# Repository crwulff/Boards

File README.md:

# Boards
1. [Pano G2 Debug Adapter](/PanoDebugAdapter) converts the 0.05" JTAG connector on these devices to 0.1" to connect to fly leads or other jumper wires.

<br/>

2. [Layer 1 Switch](/L1Switch) is a L1 switch / virtual patch panel development board. This is useful for automated testing of equipment that needs different network topologies for various tests.

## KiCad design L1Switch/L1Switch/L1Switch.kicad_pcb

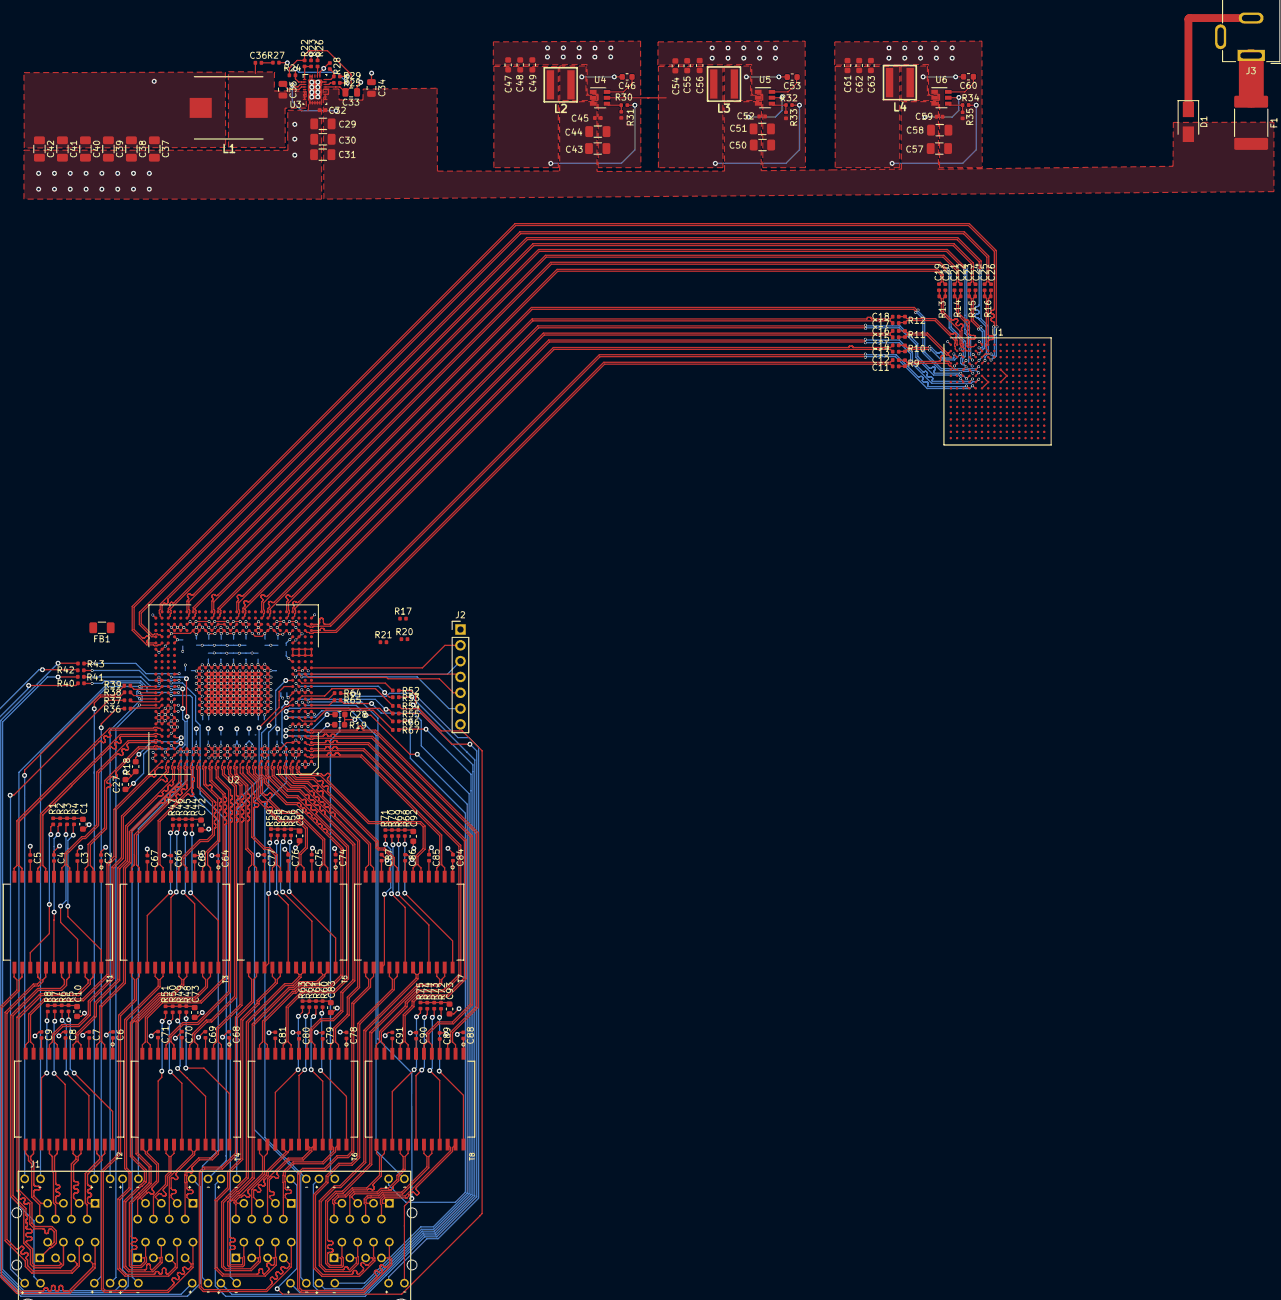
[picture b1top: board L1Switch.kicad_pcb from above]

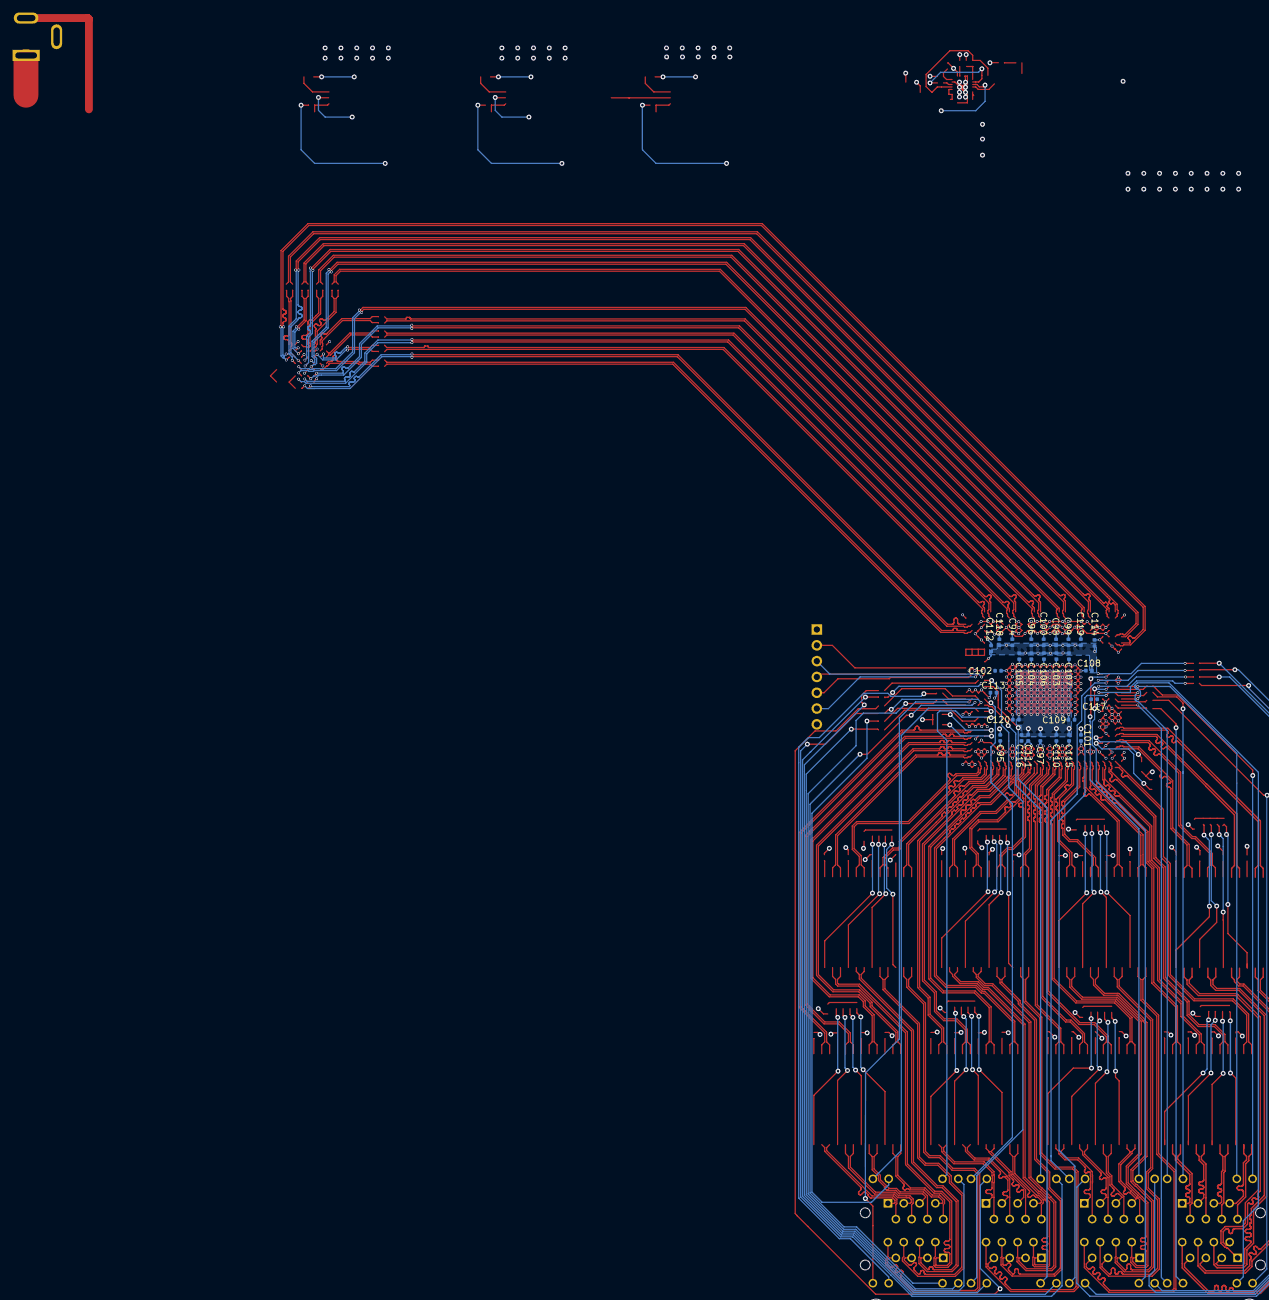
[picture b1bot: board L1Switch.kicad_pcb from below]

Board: 4 copper layers, 219 parts (27 on the bottom side), 338 nets.

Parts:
C1, C10, C72, C73, C82, C83, C92, C93: 1000pF, 2KV; C_0603_1608Metric
C2, C3, C4, C5, C6, C7, C8, C9, C11, C12, C13, C14, C15, C16, C17, C18, C19, C20, C21, C22, C23, C24, C25, C26, C64, C65, C66, C67, C68, C69, C70, C71, C74, C75, C76, C77, C78, C79, C80, C81, C84, C85, C86, C87, C88, C89, C90, C91: 0.1 uF; C_0402_1005Metric
C27, C28: 1.0 uF; C_0603_1608Metric
C29, C30, C31: 22 uF, 3.637 mΩ; C_1206_3216Metric
C32: 2.2 nF, 1.268 Ω; C_0402_1005Metric
C33, C34: 2.2 uF, 9.497 mΩ; C_0805_2012Metric
C35: 100 nF, 64 mOhm; C_0805_2012Metric
C36: 470 pF, 5.548 Ω; C_0402_1005Metric
C37, C38, C39, C40, C41, C42: 100 uF, 4.885 mΩ; C_1206_3216Metric
C43, C44, C50, C51, C57, C58: 10 uF, 4.512 mΩ; C_1206_3216Metric
C45, C52, C59: 100 nF, 1 mΩ; C_0402_1005Metric
C46, C53, C60: 100 nF, 1 mOhm; C_0603_1608Metric
C47, C48, C49, C54, C55, C56, C61, C62, C63: 22 uF, 1 mΩ; C_0603_1608Metric
C94, C95, C96, C97, C98, C99, C100, C101, C102, C103, C104, C105, C106, C107, C108, C109, C110, C111, C112, C113, C114, C115, C116, C117, C118, C119, C120: 100nF; C_0402_1005Metric
D1: P4SMA6.8CA; D_SMA
F1: 2920L700/12MR-A; Fuse_2920_7451Metric
FB1: 100 ohm @ 100 MHz, 3A; FB_1206_3216Metric
J1: RJSNEGF8A08; AMPHENOL_RJSNE-GF8X-08
J2: Conn_01x07_Male; PinHeader_1x07_P2.54mm_Vertical
J3: Barrel_Jack; MJ-179PH
L1: 1 uH, 3.5 mΩ; INDPM110100X400N
L2, L3, L4: 2.2 uH, 13.2 mΩ; XAL5030
R1, R2, R3, R4, R5, R6, R7, R8, R36, R37, R38, R39, R40, R41, R42, R43, R44, R45, R46, R47, R48, R49, R50, R51, R52, R53, R54, R55, R56, R57, R58, R59, R60, R61, R62, R63, R64, R65, R66, R67, R68, R69, R70, R71, R72, R73, R74, R75: 75R0; R_0402_1005Metric
R9, R10, R11, R12, R13, R14, R15, R16: 100R0; R_0402_1005Metric
R17, R20, R28, R29, R31, R33, R35: 10K; R_0402_1005Metric
R18, R19: 2K00 1%; R_0603_1608Metric
R21: 1K0; R_0402_1005Metric
R22: 249K; R_0402_1005Metric
R23: 44K2; R_0402_1005Metric
R24: 105K; R_0402_1005Metric
R25: 150K; R_0402_1005Metric
R26: 68K1; R_0402_1005Metric
R27: 3R01; R_0402_1005Metric
R30: 33K2; R_0402_1005Metric
R32: 13K7; R_0402_1005Metric
R34: 3K09; R_0402_1005Metric
T1, T2, T3, T4, T5, T6, T7, T8: SM51589PEL
U1: XC7A15T-FTG256; Xilinx_FTG256
U2: VSC8658
U3: TPS548A20RVE; TPS548A20RVER
U4, U5, U6: TPS565208; SOT-23-6

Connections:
+1V0: C61.1, C62.1, C63.1, L4.2, R34.1, U1.E10 (VCCBRAM), U1.F7 (VCCINT), U1.F9 (VCCINT), U1.F11 (VCCBRAM), U1.G6 (VCCINT), U1.H9 (VCCINT), U1.J6 (VCCINT), U1.K9 (VCCINT), U1.L8 (VCCINT)
+1V2: C37.1, C38.1, C39.1, C40.1, C41.1, C42.1, C102.1, C103.1, C104.1, C105.1, C106.1, C107.1, C108.1, C109.1, C120.1, FB1.2, L1.2, R28.1, U1.A6 (VCCO_35), U1.A16 (VCCO_15), U1.B3 (VCCO_35), U1.B13 (VCCO_15), U1.C10 (VCCO_15), U1.D7 (VCCO_35), U1.E4 (VCCO_35), U1.E14 (VCCO_15), U1.F1 (VCCO_35), U1.H15 (VCCO_15), U1.J2 (VCCO_35), U1.J12 (VCCO_15), U1.L16 (VCCO_14), U1.M13 (VCCO_14), U1.N10 (VCCO_14), U1.P7 (VCCO_14), U1.R14 (VCCO_14), U1.T11 (VCCO_14), U2.K8 (VDD12), U2.K19 (VDD12), U2.L8 (VDD12), U2.L19 (VDD12), U2.M8 (VDD12), U2.M19 (VDD12), U2.N8 (VDD12), U2.N19 (VDD12), U2.P8 (VDD12), U2.P19 (VDD12), U2.R8 (VDD12), U2.R19 (VDD12), U2.T8 (VDD12), U2.T19 (VDD12), U2.U8 (VDD12), U2.U9 (VDD12), U2.U10 (VDD12), U2.U11 (VDD12), U2.U12 (VDD12), U2.U13 (VDD12), U2.U14 (VDD12), U2.U15 (VDD12), U2.U16 (VDD12), U2.U17 (VDD12), U2.U18 (VDD12), U2.U19 (VDD12), U3.24 (VO)
+1V2A: C94.1, C95.1, C96.1, C97.1, C98.1, C99.1, C100.1, C101.1, C118.1, C119.1, FB1.1, U2.AB24 (VDD12A), U2.AC4 (VDD12A), U2.AC5 (VDD12A), U2.AC7 (VDD12A), U2.AC8 (VDD12A), U2.AC11 (VDD12A), U2.AC12 (VDD12A), U2.AC13 (VDD12A), U2.AC15 (VDD12A), U2.AC16 (VDD12A), U2.AC18 (VDD12A), U2.AC19 (VDD12A), U2.AC20 (VDD12A), U2.AC24 (VDD12A), U2.AD8 (VDD12A), U2.AD19 (VDD12A), U2.C7 (VDD12A), U2.C13 (VDD12A), U2.C19 (VDD12A), U2.C20 (VDD12A), U2.D6 (VDD12A), U2.D7 (VDD12A), U2.D13 (VDD12A), U2.D19 (VDD12A), U2.D20 (VDD12A), U2.D23 (VDD12A), U2.E3 (VDD12A), U2.E4 (VDD12A), U2.E24 (VDD12A)
+1V8: C54.1, C55.1, C56.1, L3.2, R32.1, U1.F8 (VCCBATT_0), U1.G8 (VCCADC_0), U1.G10 (VCCAUX), U1.J10 (VCCAUX), U1.K11 (VCCAUX), U1.L10 (VCCAUX), U4.5 (EN)
+3V3: C47.1, C48.1, C49.1, C110.1, C111.1, C112.1, C113.1, C114.1, C115.1, C116.1, C117.1, J2.1, L2.2, R17.2, R20.1, R21.1, R30.1, U1.M3 (VCCO_34), U1.R4 (VCCO_34), U1.T1 (VCCO_34), U2.AA23 (VDD33), U2.AB4 (VDDIO), U2.AB23 (VDD33), U2.AD3 (VDD33), U2.AD5 (VDD33), U2.AD7 (VDD33), U2.AD11 (VDD33), U2.AD12 (VDD33), U2.AD14 (VDD33), U2.AD17 (VDD33), U2.AD20 (VDD33), U2.AD21 (VDD33), U2.C3 (VDD33), U2.C4 (VDD33), U2.C10 (VDD33), U2.C11 (VDD33), U2.C12 (VDD33), U2.C16 (VDD33), U2.C17 (VDD33), U2.C21 (VDD33), U2.C23 (VDD33), U2.C25 (VDD33), U2.D3 (VDD33), U2.D4 (VDD33), U2.D10 (VDD33), U2.D11 (VDD33), U2.D12 (VDD33), U2.D16 (VDD33), U2.D17 (VDD33), U2.D21 (VDD33), U2.D22 (VDD33), U2.F24 (VDD33), U2.G23 (VDD33), U2.H23 (VDD33), U2.H24 (VDD33), U2.J23 (VDD33), U2.M23 (VDD33), U2.M24 (VDD33), U2.N1 (VDD33), U2.N2 (VDD33), U2.N3 (VDD33), U2.N4 (VDD33), U2.R25 (VDD33), U2.R26 (VDD33), U2.U2 (VDDIO), U2.U4 (VDD33), U2.V2 (VDDIO)
/Net 1/P1.A+: J1.11 (1-1), T1.23 (TD1+)
/Net 1/P1.A-: J1.12 (1-2), T1.22 (TD1-)
/Net 1/P1.A_CMN: R4.1, T1.24 (TCT1)
/Net 1/P1.B+: J1.13 (1-3), T1.20 (TD2+)
/Net 1/P1.B-: J1.14 (1-4), T1.19 (TD2-)
/Net 1/P1.B_CMN: R3.1, T1.21 (TCT2)
/Net 1/P1.C+: J1.15 (1-5), T1.17 (TD3+)
/Net 1/P1.C-: J1.16 (1-6), T1.16 (TD3-)
/Net 1/P1.C_CMN: R2.1, T1.18 (TCT3)
/Net 1/P1.D+: J1.17 (1-7), T1.14 (TD4+)
/Net 1/P1.D-: J1.18 (1-8), T1.13 (TD4-)
/Net 1/P1.D_CMN: R1.1, T1.15 (TCT4)
/Net 1/P1.LED0: J1.19 (1-9), U2.L26 (LED_0_0)
/Net 1/P1.LED1: R36.1, U2.L25 (LED_0_1)
/Net 1/P1.LED2: J1.111 (1-11), U2.M26 (LED_0_2)
/Net 1/P1.LED3: R37.1, U2.M25 (LED_0_3)
/Net 1/P2.A+: J1.21 (2-1), T2.23 (TD1+)
/Net 1/P2.A-: J1.22 (2-2), T2.22 (TD1-)
/Net 1/P2.A_CMN: R5.1, T2.24 (TCT1)
/Net 1/P2.B+: J1.23 (2-3), T2.20 (TD2+)
/Net 1/P2.B-: J1.24 (2-4), T2.19 (TD2-)
/Net 1/P2.B_CMN: R6.1, T2.21 (TCT2)
/Net 1/P2.C+: J1.25 (2-5), T2.17 (TD3+)
/Net 1/P2.C-: J1.26 (2-6), T2.16 (TD3-)
/Net 1/P2.C_CMN: R7.1, T2.18 (TCT3)
/Net 1/P2.D+: J1.27 (2-7), T2.14 (TD4+)
/Net 1/P2.D-: J1.28 (2-8), T2.13 (TD4-)
/Net 1/P2.D_CMN: R8.1, T2.15 (TCT4)
/Net 1/P2.LED0: J1.29 (2-9), U2.N26 (LED_1_0)
/Net 1/P2.LED1: R38.1, U2.N25 (LED_1_1)
/Net 1/P2.LED2: J1.211 (2-11), U2.P26 (LED_1_2)
/Net 1/P2.LED3: R39.1, U2.P25 (LED_1_3)
/Net 1/P3.A+: J1.31 (3-1), T3.23 (TD1+)
/Net 1/P3.A-: J1.32 (3-2), T3.22 (TD1-)
/Net 1/P3.A_CMN: R44.1, T3.24 (TCT1)
/Net 1/P3.B+: J1.33 (3-3), T3.20 (TD2+)
/Net 1/P3.B-: J1.34 (3-4), T3.19 (TD2-)
/Net 1/P3.B_CMN: R45.1, T3.21 (TCT2)
/Net 1/P3.C+: J1.35 (3-5), T3.17 (TD3+)
/Net 1/P3.C-: J1.36 (3-6), T3.16 (TD3-)
/Net 1/P3.C_CMN: R46.1, T3.18 (TCT3)
/Net 1/P3.D+: J1.37 (3-7), T3.14 (TD4+)
/Net 1/P3.D-: J1.38 (3-8), T3.13 (TD4-)
/Net 1/P3.D_CMN: R47.1, T3.15 (TCT4)
/Net 1/P3.LED0: J1.39 (3-9), U2.N24 (LED_2_0)
/Net 1/P3.LED1: R40.1, U2.N23 (LED_2_1)
/Net 1/P3.LED2: J1.311 (3-11), U2.P24 (LED_2_2)
/Net 1/P3.LED3: R41.1, U2.P23 (LED_2_3)
/Net 1/P4.A+: J1.41 (4-1), T4.23 (TD1+)
/Net 1/P4.A-: J1.42 (4-2), T4.22 (TD1-)
/Net 1/P4.A_CMN: R48.1, T4.24 (TCT1)
/Net 1/P4.B+: J1.43 (4-3), T4.20 (TD2+)
/Net 1/P4.B-: J1.44 (4-4), T4.19 (TD2-)
/Net 1/P4.B_CMN: R49.1, T4.21 (TCT2)
/Net 1/P4.C+: J1.45 (4-5), T4.17 (TD3+)
/Net 1/P4.C-: J1.46 (4-6), T4.16 (TD3-)
/Net 1/P4.C_CMN: R50.1, T4.18 (TCT3)
/Net 1/P4.D+: J1.47 (4-7), T4.14 (TD4+)
/Net 1/P4.D-: J1.48 (4-8), T4.13 (TD4-)
/Net 1/P4.D_CMN: R51.1, T4.15 (TCT4)
/Net 1/P4.LED0: J1.49 (4-9), U2.R24 (LED_3_0)
/Net 1/P4.LED1: R42.1, U2.R23 (LED_3_1)
/Net 1/P4.LED2: J1.411 (4-11), U2.T24 (LED_3_2)
/Net 1/P4.LED3: R43.1, U2.T23 (LED_3_3)
/Net 1/P5.A+: J1.51 (5-1), T5.23 (TD1+)
/Net 1/P5.A-: J1.52 (5-2), T5.22 (TD1-)
/Net 1/P5.A_CMN: R56.1, T5.24 (TCT1)
/Net 1/P5.B+: J1.53 (5-3), T5.20 (TD2+)
/Net 1/P5.B-: J1.54 (5-4), T5.19 (TD2-)
/Net 1/P5.B_CMN: R57.1, T5.21 (TCT2)
/Net 1/P5.C+: J1.55 (5-5), T5.17 (TD3+)
/Net 1/P5.C-: J1.56 (5-6), T5.16 (TD3-)
/Net 1/P5.C_CMN: R58.1, T5.18 (TCT3)
/Net 1/P5.D+: J1.57 (5-7), T5.14 (TD4+)
/Net 1/P5.D-: J1.58 (5-8), T5.13 (TD4-)
/Net 1/P5.D_CMN: R59.1, T5.15 (TCT4)
/Net 1/P5.LED0: J1.59 (5-9), U2.R4 (LED_4_0)
/Net 1/P5.LED1: R52.1, U2.R3 (LED_4_1)
/Net 1/P5.LED2: J1.511 (5-11), U2.P4 (LED_4_2)
/Net 1/P5.LED3: R53.1, U2.P3 (LED_4_3)
/Net 1/P6.A+: J1.61 (6-1), T6.23 (TD1+)
/Net 1/P6.A-: J1.62 (6-2), T6.22 (TD1-)
/Net 1/P6.A_CMN: R60.1, T6.24 (TCT1)
/Net 1/P6.B+: J1.63 (6-3), T6.20 (TD2+)
/Net 1/P6.B-: J1.64 (6-4), T6.19 (TD2-)
/Net 1/P6.B_CMN: R61.1, T6.21 (TCT2)
/Net 1/P6.C+: J1.65 (6-5), T6.17 (TD3+)
/Net 1/P6.C-: J1.66 (6-6), T6.16 (TD3-)
/Net 1/P6.C_CMN: R62.1, T6.18 (TCT3)
/Net 1/P6.D+: J1.67 (6-7), T6.14 (TD4+)
/Net 1/P6.D-: J1.68 (6-8), T6.13 (TD4-)
/Net 1/P6.D_CMN: R63.1, T6.15 (TCT4)
/Net 1/P6.LED0: J1.69 (6-9), U2.M4 (LED_5_0)
/Net 1/P6.LED1: R54.1, U2.M3 (LED_5_1)
/Net 1/P6.LED2: J1.611 (6-11), U2.L4 (LED_5_2)
/Net 1/P6.LED3: R55.1, U2.L3 (LED_5_3)
/Net 1/P7.A+: J1.71 (7-1), T7.23 (TD1+)
/Net 1/P7.A-: J1.72 (7-2), T7.22 (TD1-)
/Net 1/P7.A_CMN: R68.1, T7.24 (TCT1)
/Net 1/P7.B+: J1.73 (7-3), T7.20 (TD2+)
/Net 1/P7.B-: J1.74 (7-4), T7.19 (TD2-)
/Net 1/P7.B_CMN: R69.1, T7.21 (TCT2)
/Net 1/P7.C+: J1.75 (7-5), T7.17 (TD3+)
/Net 1/P7.C-: J1.76 (7-6), T7.16 (TD3-)
/Net 1/P7.C_CMN: R70.1, T7.18 (TCT3)
/Net 1/P7.D+: J1.77 (7-7), T7.14 (TD4+)
/Net 1/P7.D-: J1.78 (7-8), T7.13 (TD4-)
/Net 1/P7.D_CMN: R71.1, T7.15 (TCT4)
/Net 1/P7.LED0: J1.79 (7-9), U2.M2 (LED_6_0)
/Net 1/P7.LED1: R64.1, U2.M1 (LED_6_1)
/Net 1/P7.LED2: J1.711 (7-11), U2.L2 (LED_6_2)
/Net 1/P7.LED3: R65.1, U2.L1 (LED_6_3)
/Net 1/P8.A+: J1.81 (8-1), T8.23 (TD1+)
/Net 1/P8.A-: J1.82 (8-2), T8.22 (TD1-)
/Net 1/P8.A_CMN: R72.1, T8.24 (TCT1)
/Net 1/P8.B+: J1.83 (8-3), T8.20 (TD2+)
/Net 1/P8.B-: J1.84 (8-4), T8.19 (TD2-)
/Net 1/P8.B_CMN: R73.1, T8.21 (TCT2)
/Net 1/P8.C+: J1.85 (8-5), T8.17 (TD3+)
/Net 1/P8.C-: J1.86 (8-6), T8.16 (TD3-)
/Net 1/P8.C_CMN: R74.1, T8.18 (TCT3)
/Net 1/P8.D+: J1.87 (8-7), T8.14 (TD4+)
/Net 1/P8.D-: J1.88 (8-8), T8.13 (TD4-)
/Net 1/P8.D_CMN: R75.1, T8.15 (TCT4)
/Net 1/P8.LED0: J1.89 (8-9), U2.K4 (LED_7_0)
/Net 1/P8.LED1: R66.1, U2.K3 (LED_7_1)
/Net 1/P8.LED2: J1.811 (8-11), U2.J4 (LED_7_2)
/Net 1/P8.LED3: R67.1, U2.J3 (LED_7_3)
/Net 1/RD_N0: C26.2, U2.AB26 (MAC_RDN_0)
/Net 1/RD_N1: C24.2, U2.AF24 (MAC_RDN_1)
/Net 1/RD_N2: C22.2, U2.AF20 (MAC_RDN_2)
/Net 1/RD_N3: C20.2, U2.AF16 (MAC_RDN_3)
/Net 1/RD_N4: C18.2, U2.AF12 (MAC_RDN_4)
/Net 1/RD_N5: C16.2, U2.AF8 (MAC_RDN_5)
/Net 1/RD_N6: C14.2, U2.AF4 (MAC_RDN_6)
/Net 1/RD_N7: C12.2, U2.AC1 (MAC_RDN_7)
/Net 1/RD_P0: C25.2, U2.AB25 (MAC_RDP_0)
/Net 1/RD_P1: C23.2, U2.AE24 (MAC_RDP_1)
/Net 1/RD_P2: C21.2, U2.AE20 (MAC_RDP_2)
/Net 1/RD_P3: C19.2, U2.AE16 (MAC_RDP_3)
/Net 1/RD_P4: C17.2, U2.AE12 (MAC_RDP_4)
/Net 1/RD_P5: C15.2, U2.AE8 (MAC_RDP_5)
/Net 1/RD_P6: C13.2, U2.AE4 (MAC_RDP_6)
/Net 1/RD_P7: C11.2, U2.AC2 (MAC_RDP_7)
/Net 1/TXVA_N0: T1.3 (MX1-), U2.D25 (TXVNA_0)
/Net 1/TXVA_N1: T2.3 (MX1-), U2.B22 (TXVNA_1)
/Net 1/TXVA_N2: T3.3 (MX1-), U2.B18 (TXVNA_2)
/Net 1/TXVA_N3: T4.3 (MX1-), U2.B14 (TXVNA_3)
/Net 1/TXVA_N4: T5.3 (MX1-), U2.B10 (TXVNA_4)
/Net 1/TXVA_N5: T6.3 (MX1-), U2.B6 (TXVNA_5)
/Net 1/TXVA_N6: T7.3 (MX1-), U2.C2 (TXVNA_6)
/Net 1/TXVA_N7: T8.3 (MX1-), U2.G2 (TXVNA_7)
/Net 1/TXVA_P0: T1.2 (MX1+), U2.D26 (TXVPA_0)
/Net 1/TXVA_P1: T2.2 (MX1+), U2.A22 (TXVPA_1)
/Net 1/TXVA_P2: T3.2 (MX1+), U2.A18 (TXVPA_2)
/Net 1/TXVA_P3: T4.2 (MX1+), U2.A14 (TXVPA_3)
/Net 1/TXVA_P4: T5.2 (MX1+), U2.A10 (TXVPA_4)
/Net 1/TXVA_P5: T6.2 (MX1+), U2.A6 (TXVPA_5)
/Net 1/TXVA_P6: T7.2 (MX1+), U2.C1 (TXVPA_6)
/Net 1/TXVA_P7: T8.2 (MX1+), U2.G1 (TXVPA_7)
/Net 1/TXVB_N0: T1.6 (MX2-), U2.E25 (TXVNB_0)
/Net 1/TXVB_N1: T2.6 (MX2-), U2.B23 (TXVNB_1)
/Net 1/TXVB_N2: T3.6 (MX2-), U2.B19 (TXVNB_2)
/Net 1/TXVB_N3: T4.6 (MX2-), U2.B15 (TXVNB_3)
/Net 1/TXVB_N4: T5.6 (MX2-), U2.B11 (TXVNB_4)
/Net 1/TXVB_N5: T6.6 (MX2-), U2.B7 (TXVNB_5)
/Net 1/TXVB_N6: T7.6 (MX2-), U2.B3 (TXVNB_6)
/Net 1/TXVB_N7: T8.6 (MX2-), U2.F2 (TXVNB_7)
/Net 1/TXVB_P0: T1.5 (MX2+), U2.E26 (TXVPB_0)
/Net 1/TXVB_P1: T2.5 (MX2+), U2.A23 (TXVPB_1)
/Net 1/TXVB_P2: T3.5 (MX2+), U2.A19 (TXVPB_2)
/Net 1/TXVB_P3: T4.5 (MX2+), U2.A15 (TXVPB_3)
/Net 1/TXVB_P4: T5.5 (MX2+), U2.A11 (TXVPB_4)
/Net 1/TXVB_P5: T6.5 (MX2+), U2.A7 (TXVPB_5)
/Net 1/TXVB_P6: T7.5 (MX2+), U2.A3 (TXVPB_6)
/Net 1/TXVB_P7: T8.5 (MX2+), U2.F1 (TXVPB_7)
/Net 1/TXVC_N0: T1.9 (MX3-), U2.F25 (TXVNC_0)
/Net 1/TXVC_N1: T2.9 (MX3-), U2.B24 (TXVNC_1)
/Net 1/TXVC_N2: T3.9 (MX3-), U2.B20 (TXVNC_2)
/Net 1/TXVC_N3: T4.9 (MX3-), U2.B16 (TXVNC_3)
/Net 1/TXVC_N4: T5.9 (MX3-), U2.B12 (TXVNC_4)
/Net 1/TXVC_N5: T6.9 (MX3-), U2.B8 (TXVNC_5)
/Net 1/TXVC_N6: T7.9 (MX3-), U2.B4 (TXVNC_6)
/Net 1/TXVC_N7: T8.9 (MX3-), U2.E2 (TXVNC_7)
/Net 1/TXVC_P0: T1.8 (MX3+), U2.F26 (TXVPC_0)
/Net 1/TXVC_P1: T2.8 (MX3+), U2.A24 (TXVPC_1)
/Net 1/TXVC_P2: T3.8 (MX3+), U2.A20 (TXVPC_2)
/Net 1/TXVC_P3: T4.8 (MX3+), U2.A16 (TXVPC_3)
/Net 1/TXVC_P4: T5.8 (MX3+), U2.A12 (TXVPC_4)
/Net 1/TXVC_P5: T6.8 (MX3+), U2.A8 (TXVPC_5)
/Net 1/TXVC_P6: T7.8 (MX3+), U2.A4 (TXVPC_6)
/Net 1/TXVC_P7: T8.8 (MX3+), U2.E1 (TXVPC_7)
/Net 1/TXVD_N0: T1.12 (MX4-), U2.G25 (TXVND_0)
/Net 1/TXVD_N1: T2.12 (MX4-), U2.B25 (TXVND_1)
/Net 1/TXVD_N2: T3.12 (MX4-), U2.B21 (TXVND_2)
/Net 1/TXVD_N3: T4.12 (MX4-), U2.B17 (TXVND_3)
/Net 1/TXVD_N4: T5.12 (MX4-), U2.B13 (TXVND_4)
/Net 1/TXVD_N5: T6.12 (MX4-), U2.B9 (TXVND_5)
/Net 1/TXVD_N6: T7.12 (MX4-), U2.B5 (TXVND_6)
/Net 1/TXVD_N7: T8.12 (MX4-), U2.D2 (TXVND_7)
/Net 1/TXVD_P0: T1.11 (MX4+), U2.G26 (TXVPD_0)
/Net 1/TXVD_P1: T2.11 (MX4+), U2.A25 (TXVPD_1)
/Net 1/TXVD_P2: T3.11 (MX4+), U2.A21 (TXVPD_2)
/Net 1/TXVD_P3: T4.11 (MX4+), U2.A17 (TXVPD_3)
/Net 1/TXVD_P4: T5.11 (MX4+), U2.A13 (TXVPD_4)
/Net 1/TXVD_P5: T6.11 (MX4+), U2.A9 (TXVPD_5)
/Net 1/TXVD_P6: T7.11 (MX4+), U2.A5 (TXVPD_6)
/Net 1/TXVD_P7: T8.11 (MX4+), U2.D1 (TXVPD_7)
/PHY0_REFCLK: U1.M1 (IO_L2N_T0_34), U2.J1 (XTAL1/REFCLK)
/PHY_MDC: U1.L5 (IO_0_34), U2.U3 (MDC)
/PHY_MDINT_N: R17.1, U1.M4 (IO_L1N_T0_34), U2.W1 (MDINT_0), U2.W2 (MDINT_1), U2.W3 (MDINT_2), U2.W4 (MDINT_3), U2.Y1 (MDINT_4), U2.Y2 (MDINT_5), U2.Y3 (MDINT_6), U2.Y4 (MDINT_7)
/PHY_MDIO: R21.2, U1.L4 (IO_L1P_T0_34), U2.V3 (MDIO)
/PHY_RESET_N: U1.M2 (IO_L2P_T0_34), U2.AA3 (NRESET)
/Power/VIN_5V: C29.1, C30.1, C31.1, C32.1, C34.1, C43.1, C44.1, C45.1, C50.1, C51.1, C52.1, C57.1, C58.1, C59.1, D1.2 (A2), F1.2, U3.3 (EN), U3.15 (VIN), U3.16 (VIN), U3.17 (VIN), U3.19 (VDD), U4.3 (VIN), U5.3 (VIN), U5.5 (EN), U6.3 (VIN), U6.5 (EN)
/SGMII.RD_N0: C26.1, R16.1, U1.A7 (IO_L1N_T0_AD4N_35)
/SGMII.RD_N1: C24.1, R15.1, U1.B5 (IO_L2N_T0_AD12N_35)
/SGMII.RD_N2: C22.1, R14.1, U1.A4 (IO_L3N_T0_DQS_AD5N_35)
/SGMII.RD_N3: C20.1, R13.1, U1.A3 (IO_L4N_T0_35)
/SGMII.RD_N4: C18.1, R12.1, U1.A2 (IO_L8N_T1_AD14N_35)
/SGMII.RD_N5: C16.1, R11.1, U1.B1 (IO_L9N_T1_DQS_AD7N_35)
/SGMII.RD_N6: C14.1, R10.1, U1.C2 (IO_L7N_T1_AD6N_35)
/SGMII.RD_N7: C12.1, R9.1, U1.D1 (IO_L10N_T1_AD15N_35)
/SGMII.RD_P0: C25.1, R16.2, U1.B7 (IO_L1P_T0_AD4P_35)
/SGMII.RD_P1: C23.1, R15.2, U1.B6 (IO_L2P_T0_AD12P_35)
/SGMII.RD_P2: C21.1, R14.2, U1.A5 (IO_L3P_T0_DQS_AD5P_35)
/SGMII.RD_P3: C19.1, R13.2, U1.B4 (IO_L4P_T0_35)
/SGMII.RD_P4: C17.1, R12.2, U1.B2 (IO_L8P_T1_AD14P_35)
/SGMII.RD_P5: C15.1, R11.2, U1.C1 (IO_L9P_T1_DQS_AD7P_35)
/SGMII.RD_P6: C13.1, R10.2, U1.C3 (IO_L7P_T1_AD6P_35)
/SGMII.RD_P7: C11.1, R9.2, U1.E2 (IO_L10P_T1_AD15P_35)
/SGMII.TD_N0: U1.C6 (IO_L5N_T0_AD13N_35), U2.AA26 (MAC_TDN_0)
/SGMII.TD_N1: U1.D5 (IO_L6N_T0_VREF_35), U2.AF25 (MAC_TDN_1)
/SGMII.TD_N2: U1.C4 (IO_L12N_T1_MRCC_35), U2.AF21 (MAC_TDN_2)
/SGMII.TD_N3: U1.D3 (IO_L11N_T1_SRCC_35), U2.AF17 (MAC_TDN_3)
/SGMII.TD_N4: U1.E5 (IO_L13N_T2_MRCC_35), U2.AF13 (MAC_TDN_4)
/SGMII.TD_N5: U1.F3 (IO_L14N_T2_SRCC_35), U2.AF9 (MAC_TDN_5)
/SGMII.TD_N6: U1.G4 (IO_L16N_T2_35), U2.AF5 (MAC_TDN_6)
/SGMII.TD_N7: U1.H4 (IO_L18N_T2_35), U2.AD1 (MAC_TDN_7)
/SGMII.TD_P0: U1.C7 (IO_L5P_T0_AD13P_35), U2.AA25 (MAC_TDP_0)
/SGMII.TD_P1: U1.D6 (IO_L6P_T0_35), U2.AE25 (MAC_TDP_1)
/SGMII.TD_P2: U1.D4 (IO_L12P_T1_MRCC_35), U2.AE21 (MAC_TDP_2)
/SGMII.TD_P3: U1.E3 (IO_L11P_T1_SRCC_35), U2.AE17 (MAC_TDP_3)
/SGMII.TD_P4: U1.F5 (IO_L13P_T2_MRCC_35), U2.AE13 (MAC_TDP_4)
/SGMII.TD_P5: U1.F4 (IO_L14P_T2_SRCC_35), U2.AE9 (MAC_TDP_5)
/SGMII.TD_P6: U1.G5 (IO_L16P_T2_35), U2.AE5 (MAC_TDP_6)
/SGMII.TD_P7: U1.H5 (IO_L18P_T2_35), U2.AD2 (MAC_TDP_7)
GND: C2.1, C3.1, C4.1, C5.1, C6.1, C7.1, C8.1, C9.1, C27.2, C28.2, C29.2, C30.2, C31.2, C32.2, C33.2, C34.2, C37.2, C38.2, C39.2, C40.2, C41.2, C42.2, C43.2, C44.2, C45.2, C47.2, C48.2, C49.2, C50.2, C51.2, C52.2, C54.2, C55.2, C56.2, C57.2, C58.2, C59.2, C61.2, C62.2, C63.2, C64.1, C65.1, C66.1, C67.1, C68.1, C69.1, C70.1, C71.1, C74.1, C75.1, C76.1, C77.1, C78.1, C79.1, C80.1, C81.1, C84.1, C85.1, C86.1, C87.1, C88.1, C89.1, C90.1, C91.1, C94.2, C95.2, C96.2, C97.2, C98.2, C99.2, C100.2, C101.2, C102.2, C103.2, C104.2, C105.2, C106.2, C107.2, C108.2, C109.2, C110.2, C111.2, C112.2, C113.2, C114.2, C115.2, C116.2, C117.2, C118.2, C119.2, C120.2, D1.1 (A1), J2.7, J3.2, R18.1, R19.1, R23.2, R26.2, R27.2, R29.2, R31.2, R33.2, R35.2, U1.A1 (GND), U1.A11 (GND), U1.B8 (GND), U1.C5 (GND), U1.C15 (GND), U1.D2 (GND), U1.D12 (GND), U1.E9 (GND), U1.F6 (GND), U1.F10 (GND), U1.F16 (GND), U1.G3 (GND), U1.G7 (GNDADC_0), U1.G9 (GND), U1.G13 (GND), U1.H6 (GND), U1.J9 (GND), U1.J11 (GND), U1.K4 (GND), U1.K6 (GND), U1.K14 (GND), U1.L1 (GND), U1.L11 (GND), U1.M8 (GND), U1.N5 (GND), U1.N15 (GND), U1.P2 (GND), U1.P12 (GND), U1.R9 (GND), U1.T6 (GND), U1.T16 (GND), U2.A2 (VSS), U2.AA4 (VSS), U2.AA24 (VSS), U2.AB3 (VSS), U2.AC3 (VSS), U2.AC6 (VSS), U2.AC9 (VSS), U2.AC10 (VSS), U2.AC14 (VSS), U2.AC17 (VSS), U2.AC21 (VSS), U2.AC22 (VSS), U2.AC23 (VSS), U2.AD4 (VSS), U2.AD6 (VSS), U2.AD9 (VSS), U2.AD10 (VSS), U2.AD13 (VSS), U2.AD15 (VSS), U2.AD16 (VSS), U2.AD18 (VSS), U2.AD22 (VSS), U2.AD23 (VSS), U2.AD24 (VSS), U2.AE1 (VSS), U2.AE26 (VSS), U2.B1 (VSS), U2.B2 (VSS), U2.B26 (VSS), U2.C5 (VSS), U2.C8 (VSS), U2.C9 (VSS), U2.C14 (VSS), U2.C15 (VSS), U2.C18 (VSS), U2.C24 (VSS), U2.C26 (VSS), U2.D5 (VSS), U2.D8 (VSS), U2.D9 (VSS), U2.D14 (VSS), U2.D15 (VSS), U2.D18 (VSS), U2.D24 (VSS), U2.F3 (VSS), U2.H1 (VSS), U2.H2 (VSS), U2.H3 (VSS), U2.H4 (VSS), U2.H25 (CMODE7), U2.H26 (VSS), U2.J24 (CMODE6), U2.J25 (CMODE5), U2.J26 (CMODE4), U2.K1 (VSS), U2.K2 (VSS), U2.K9 (VSS), U2.K10 (VSS), U2.K11 (VSS), U2.K12 (VSS), U2.K13 (VSS), U2.K14 (VSS), U2.K15 (VSS), U2.K16 (VSS), U2.K17 (VSS), U2.K18 (VSS), U2.K23 (VSS), U2.K24 (CMODE3), U2.K25 (CMODE2), U2.K26 (CMODE1), U2.L9 (VSS), U2.L10 (VSS), U2.L11 (VSS), U2.L12 (VSS), U2.L13 (VSS), U2.L14 (VSS), U2.L15 (VSS), U2.L16 (VSS), U2.L17 (VSS), U2.L18 (VSS), U2.L23 (VSS), U2.L24 (CMODE0), U2.M9 (VSS), U2.M10 (VSS), U2.M11 (VSS), U2.M12 (VSS), U2.M13 (VSS), U2.M14 (VSS), U2.M15 (VSS), U2.M16 (VSS), U2.M17 (VSS), U2.M18 (VSS), U2.N9 (VSS), U2.N10 (VSS), U2.N11 (VSS), U2.N12 (VSS), U2.N13 (VSS), U2.N14 (VSS), U2.N15 (VSS), U2.N16 (VSS), U2.N17 (VSS), U2.N18 (VSS), U2.P9 (VSS), U2.P10 (VSS), U2.P11 (VSS), U2.P12 (VSS), U2.P13 (VSS), U2.P14 (VSS), U2.P15 (VSS), U2.P16 (VSS), U2.P17 (VSS), U2.P18 (VSS), U2.R9 (VSS), U2.R10 (VSS), U2.R11 (VSS), U2.R12 (VSS), U2.R13 (VSS), U2.R14 (VSS), U2.R15 (VSS), U2.R16 (VSS), U2.R17 (VSS), U2.R18 (VSS), U2.T9 (VSS), U2.T10 (VSS), U2.T11 (VSS), U2.T12 (VSS), U2.T13 (VSS), U2.T14 (VSS), U2.T15 (VSS), U2.T16 (VSS), U2.T17 (VSS), U2.T18 (VSS), U2.V4 (VSS), U2.Y25 (VSS), U2.Y26 (VSS), U3.10 (PGND), U3.11 (PGND), U3.12 (PGND), U3.13 (PGND), U3.14 (PGND), U3.22 (GND), U3.27 (GND1), U3.28 (GND2), U3.29 (PAD), U4.1 (GND), U5.1 (GND), U6.1 (GND)
GNDPWR: C1.2, C10.2, C72.2, C73.2, C82.2, C83.2, C92.2, C93.2
unnamed: C1.1, R1.2, R2.2, R3.2, R4.2
unnamed: C2.2, T1.1 (MCT1)
unnamed: C3.2, T1.4 (MCT2)
unnamed: C4.2, T1.7 (MCT3)
unnamed: C5.2, T1.10 (MCT4)
unnamed: C6.2, T2.1 (MCT1)
unnamed: C7.2, T2.4 (MCT2)
unnamed: C8.2, T2.7 (MCT3)
unnamed: C9.2, T2.10 (MCT4)
unnamed: C10.1, R5.2, R6.2, R7.2, R8.2
unnamed: C27.1, U2.E23 (REF_FILT_A)
unnamed: C28.1, U2.G4 (REF_FILT_B)
unnamed: C33.1, R22.1, R24.1, U3.20 (VREG)
unnamed: C35.1, U3.4 (VBST)
unnamed: C35.2, C36.1, L1.1, U3.6 (SW), U3.7 (SW), U3.8 (SW), U3.9 (SW)
unnamed: C36.2, R27.1
unnamed: C46.1, U4.6 (VBST)
unnamed: C46.2, L2.1, U4.2 (SW)
unnamed: C53.1, U5.6 (VBST)
unnamed: C53.2, L3.1, U5.2 (SW)
unnamed: C60.1, U6.6 (VBST)
unnamed: C60.2, L4.1, U6.2 (SW)
unnamed: C64.2, T3.1 (MCT1)
unnamed: C65.2, T3.4 (MCT2)
unnamed: C66.2, T3.7 (MCT3)
unnamed: C67.2, T3.10 (MCT4)
unnamed: C68.2, T4.1 (MCT1)
unnamed: C69.2, T4.4 (MCT2)
unnamed: C70.2, T4.7 (MCT3)
unnamed: C71.2, T4.10 (MCT4)
unnamed: C72.1, R44.2, R45.2, R46.2, R47.2
unnamed: C73.1, R48.2, R49.2, R50.2, R51.2
unnamed: C74.2, T5.1 (MCT1)
unnamed: C75.2, T5.4 (MCT2)
unnamed: C76.2, T5.7 (MCT3)
unnamed: C77.2, T5.10 (MCT4)
unnamed: C78.2, T6.1 (MCT1)
unnamed: C79.2, T6.4 (MCT2)
unnamed: C80.2, T6.7 (MCT3)
unnamed: C81.2, T6.10 (MCT4)
unnamed: C82.1, R56.2, R57.2, R58.2, R59.2
unnamed: C83.1, R60.2, R61.2, R62.2, R63.2
unnamed: C84.2, T7.1 (MCT1)
unnamed: C85.2, T7.4 (MCT2)
unnamed: C86.2, T7.7 (MCT3)
unnamed: C87.2, T7.10 (MCT4)
unnamed: C88.2, T8.1 (MCT1)
unnamed: C89.2, T8.4 (MCT2)
unnamed: C90.2, T8.7 (MCT3)
unnamed: C91.2, T8.10 (MCT4)
unnamed: C92.1, R68.2, R69.2, R70.2, R71.2
unnamed: C93.1, R72.2, R73.2, R74.2, R75.2
unnamed: F1.1, J3.1
unnamed: J1.110 (1-10), R36.2
unnamed: J1.112 (1-12), R37.2
unnamed: J1.210 (2-10), R38.2
unnamed: J1.212 (2-12), R39.2
unnamed: J1.310 (3-10), R40.2
unnamed: J1.312 (3-12), R41.2
unnamed: J1.410 (4-10), R42.2
unnamed: J1.412 (4-12), R43.2
unnamed: J1.510 (5-10), R52.2
unnamed: J1.512 (5-12), R53.2
unnamed: J1.610 (6-10), R54.2
unnamed: J1.612 (6-12), R55.2
unnamed: J1.710 (7-10), R64.2
unnamed: J1.712 (7-12), R65.2
unnamed: J1.810 (8-10), R66.2
unnamed: J1.812 (8-12), R67.2
unnamed: J2.2, U2.U1 (TDI)
unnamed: J2.3, U2.T4 (TDO)
unnamed: J2.4, U2.T1 (TMS)
unnamed: J2.5, U2.T2 (TCK)
unnamed: J2.6, U2.T3 (NTRST)
unnamed: R18.2, U2.F23 (REF_REXT_A)
unnamed: R19.2, U2.F4 (REF_REXT_B)
unnamed: R20.2, U2.R1 (PLLMODE)
unnamed: R22.2, R23.1, U3.1 (RF)
unnamed: R24.2, R25.2, U3.2 (PGOOD)
unnamed: R25.1, U3.21 (MODE)
unnamed: R26.1, U3.25 (TRIP)
unnamed: R28.2, R29.1, U3.23 (FB)
unnamed: R30.2, R31.1, U4.4 (VFB)
unnamed: R32.2, R33.1, U5.4 (VFB)
unnamed: R34.2, R35.1, U6.4 (VFB)

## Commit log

2019-05-24 Pano Debug Adapter board (6 pin 0.05" to 6 pin 0.10")
2020-04-27 Add L1 Switch board (some magnetics/jacks/PHY hooked up.)
2020-04-30 Add 1V2 power supply.
2020-05-03 Added power supplies.
2020-05-17 Kicad schema update.
2020-05-17 Connect/route 8 ports to PHY.
2020-05-18 SGMII 0 Rx/Tx routed to FPGA.
2020-05-19 Add decoupling caps and ferrite bead. Clean up reference designators.
2020-05-21 Add some step models.
2020-05-24 Length match some pairs.
2020-06-13 Layout replicated to Net2.
2020-06-15 Add instance 3 and 4 of the network ports.
2020-06-16 Assign and route pins through SGMII2.
2020-06-17 Most signals routed.
2020-06-18 Add some more cad/step models, and fix XO pinout (was flipped.)
2020-06-18 Clean up duplicate vias/tracks.
2020-06-19 Switch to XC7A35T. Update some layout constraints for 4pcb.com capabilities.
2020-06-19 Added return path vias. Updated all paths for spacing.
2020-06-20 Added power-on-reset circuit.
2020-06-21 Add FPGA decoupling caps. Add some power planes.
2020-06-21 Add most of the rest of the power planes.
2020-06-23 Add some part info. Fix footprint size for 2kV caps. Add a plane cutout around the magnetics.
2020-06-25 Update part numbers.
2020-06-25 Finish length matching. Move the layout onto a larger sheet to fit.
2020-06-25 Add board info to silkscreen.
2020-06-25 Generate production files for L1S32 REV-A.
2020-07-03 Update solder mask clearance on fine pins to allow mask bridge. Remove thermal relief on power jack and fan connector pins.
2020-07-27 Swap fan connector orientation. Add PU/PD for JTAG pins.
2020-08-02 Update RJ45 pinout on schematic and partial layout update.
2020-08-16 Add SPI flash programming instructions.
2020-08-17 First PHY port pairs remapped and all DRC fixed.
2020-08-18 Finish replicating the port rewiring and clean up some more DRC errors.
2020-08-19 More DRC cleanup.
2020-08-21 DRC cleanup.
2020-08-22 DRC cleanup complete.
2020-08-24 Add PWR_FLAG to clean up ERC errors about undriven nets. Change R269 from 100K0 to 10K0.
2020-08-25 Update voltage monitoring.
2020-12-29 Initial FPGA code.
2020-12-30 Add top-level README.
2021-04-10 Add the start of a CPU ethernet adapter (only has 8b10b coding so far, S_AXI just generated and not useful yet.)
